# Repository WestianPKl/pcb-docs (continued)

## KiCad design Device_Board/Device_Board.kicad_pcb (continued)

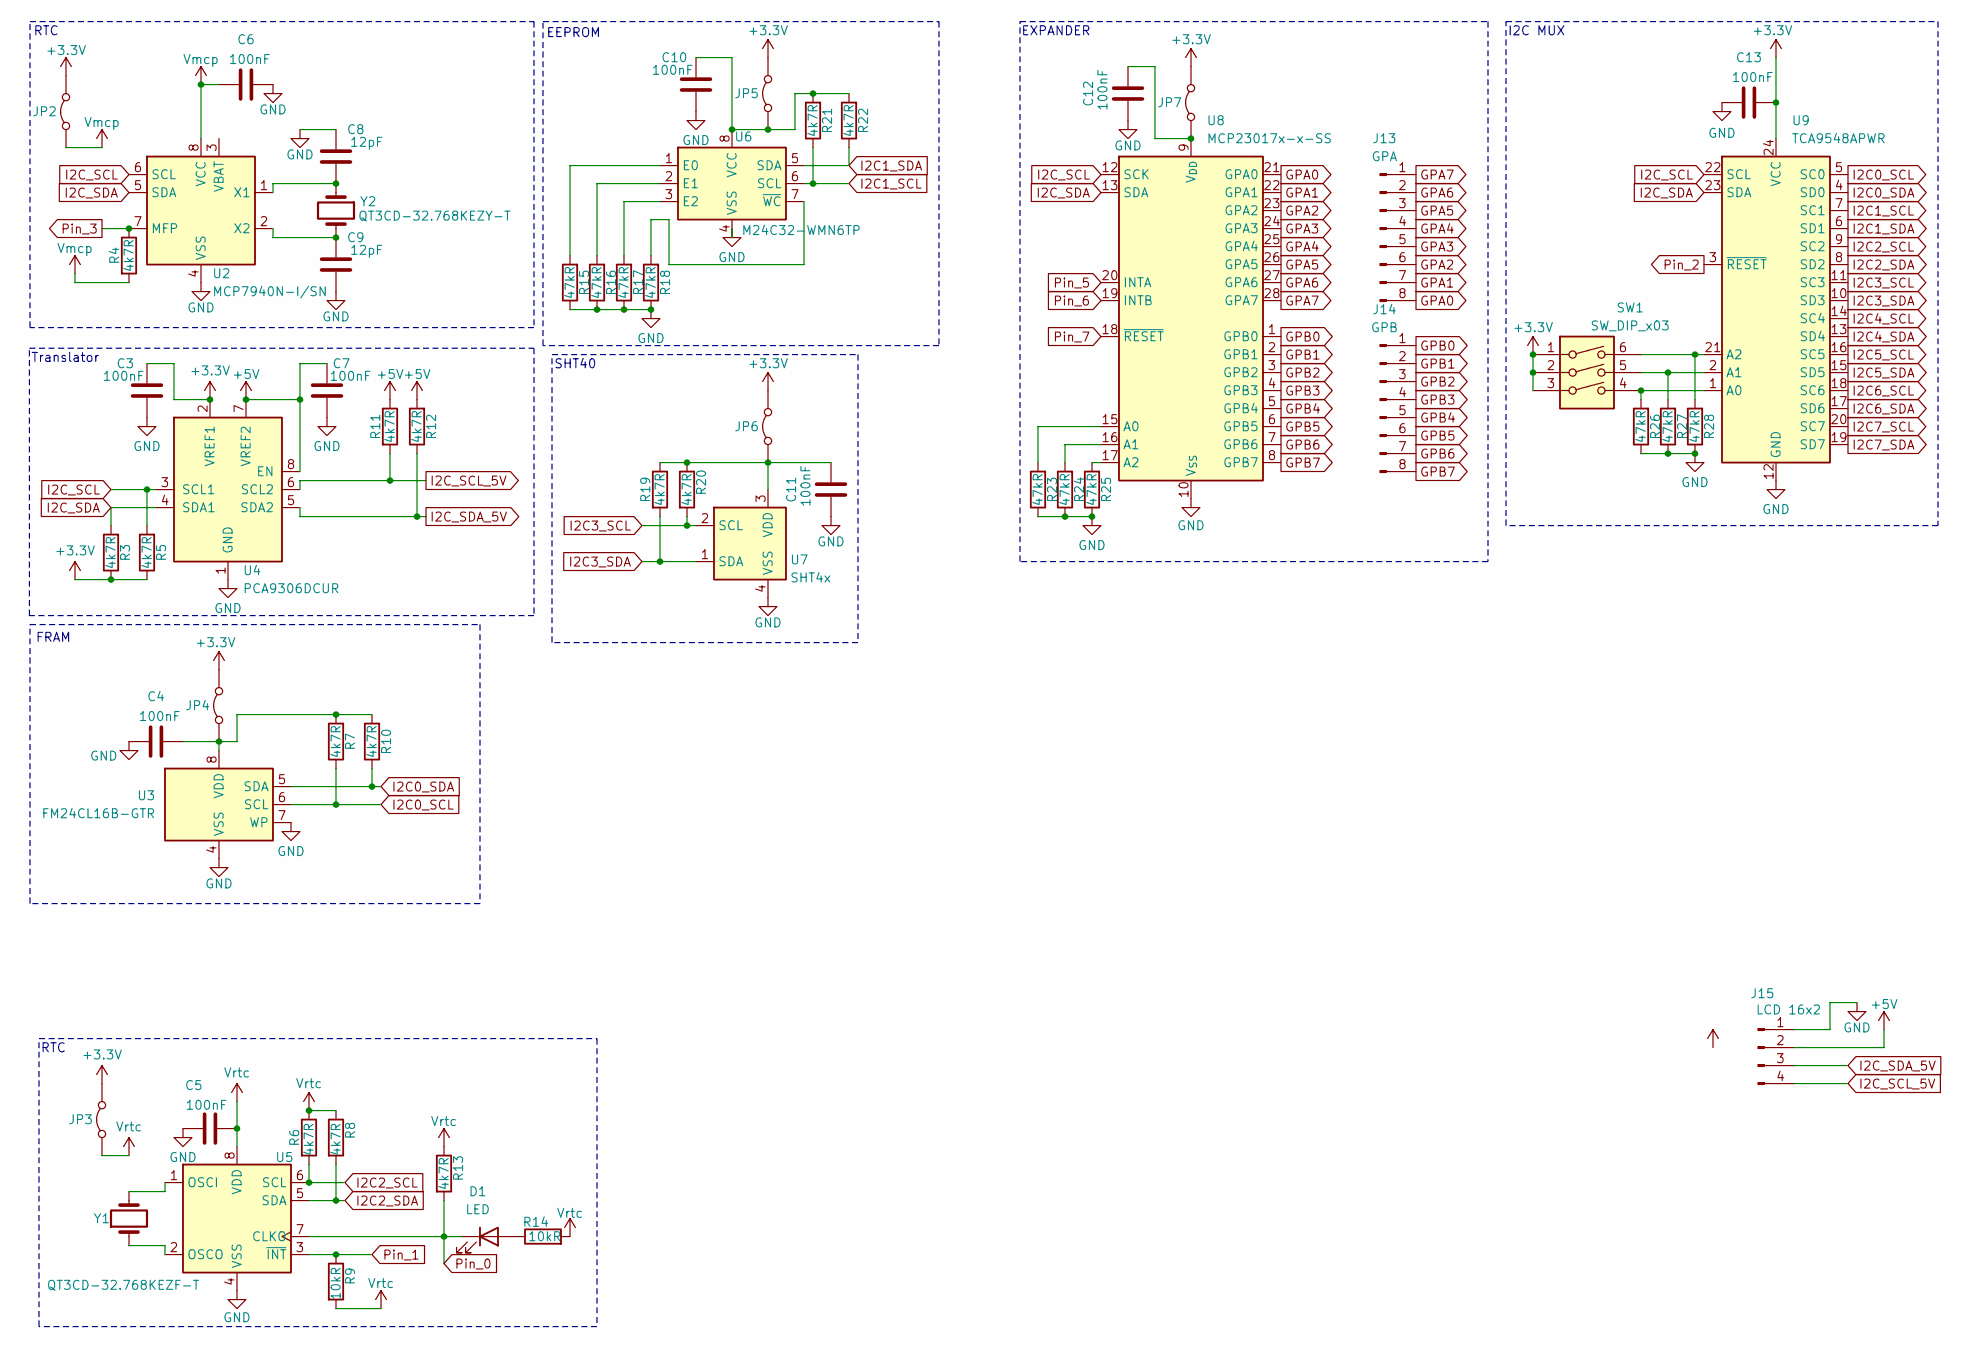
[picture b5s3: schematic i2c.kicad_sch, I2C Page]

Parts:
C3, C4, C5, C6, C7, C10, C11, C12, C13: 100nF; C_0603_1608Metric
C8, C9: 12pF; C_0603_1608Metric
D1: LED; LED_0603_1608Metric
J13: GPA; PinHeader_1x08_P2.54mm_Vertical
J14: GPB; PinHeader_1x08_P2.54mm_Vertical
J15: LCD 16x2; PinHeader_1x04_P2.54mm_Vertical
JP2, JP3, JP4, JP5, JP6, JP7: Jumper_2_Bridged; PinHeader_1x02_P2.54mm_Vertical
R3, R4, R5, R6, R7, R8, R10, R11, R12, R13, R19, R20, R21, R22: 4k7R; R_0603_1608Metric
R9, R14: 10kR; R_0603_1608Metric
R15, R16, R17, R18, R23, R24, R25, R26, R27, R28: 47kR; R_0603_1608Metric
SW1: SW_DIP_x03; SW_DIP_SPSTx03_Slide_9.78x9.8mm_W7.62mm_P2.54mm
U2: MCP7940N-I/SN; SOIC-8_3.9x4.9mm_P1.27mm
U3: FM24CL16B-GTR; SOIC-8_3.9x4.9mm_P1.27mm
U4: PCA9306DCUR; VSSOP-8_2.3x2mm_P0.5mm
U5: PCF8563T; SOIC-8_3.9x4.9mm_P1.27mm
U6: M24C32-WMN6TP; SOIC-8_3.9x4.9mm_P1.27mm
U7: SHT4x; Sensirion_DFN-4_1.5x1.5mm_P0.8mm_SHT4x_NoCentralPad
U8: MCP23017x-x-SS; SSOP-28_5.3x10.2mm_P0.65mm
U9: TCA9548APWR; TSSOP-24_4.4x7.8mm_P0.65mm
Y1: QT3CD-32.768KEZF-T; Crystal_SMD_3215-2Pin_3.2x1.5mm
Y2: QT3CD-32.768KEZY-T; Crystal_SMD_3215-2Pin_3.2x1.5mm

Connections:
+3.3V: C3.1, C13.1, JP2.2 (B), JP3.2 (B), JP4.2 (B), JP5.2 (B), JP6.2 (B), JP7.2 (B), R3.1, R5.1, SW1.1, SW1.2, SW1.3, U4.2 (VREF1), U9.24 (VCC); also elsewhere on the board
+5V: C7.1, J15.2, R11.1, R12.2, U4.7 (VREF2), U4.8 (EN); also elsewhere on the board
GND: C3.2, C4.2, C5.2, C6.1, C7.2, C8.2, C9.1, C10.2, C11.2, C12.2, C13.2, J15.1, R15.1, R16.1, R17.1, R18.1, R23.1, R24.1, R25.1, R26.1, R27.1, R28.1, U2.4 (VSS), U3.4 (VSS), U3.7 (WP), U4.1 (GND), U5.4 (VSS), U6.4 (VSS), U7.4 (VSS), U8.10 (V_{SS}), U9.12 (GND); also elsewhere on the board
GPA0: J13.8, U8.21 (GPA0)
GPA1: J13.7, U8.22 (GPA1)
GPA2: J13.6, U8.23 (GPA2)
GPA3: J13.5, U8.24 (GPA3)
GPA4: J13.4, U8.25 (GPA4)
GPA5: J13.3, U8.26 (GPA5)
GPA6: J13.2, U8.27 (GPA6)
GPA7: J13.1, U8.28 (GPA7)
GPB0: J14.1, U8.1 (GPB0)
GPB1: J14.2, U8.2 (GPB1)
GPB2: J14.3, U8.3 (GPB2)
GPB3: J14.4, U8.4 (GPB3)
GPB4: J14.5, U8.5 (GPB4)
GPB5: J14.6, U8.6 (GPB5)
GPB6: J14.7, U8.7 (GPB6)
GPB7: J14.8, U8.8 (GPB7)
I2C0_SCL: R7.1, U3.6 (SCL), U9.5 (SC0)
I2C0_SDA: R10.1, U3.5 (SDA), U9.4 (SD0)
I2C1_SCL: R21.1, U6.6 (SCL), U9.7 (SC1)
I2C1_SDA: R22.1, U6.5 (SDA), U9.6 (SD1)
I2C2_SCL: R6.2, U5.6 (SCL), U9.9 (SC2)
I2C2_SDA: R8.2, U5.5 (SDA), U9.8 (SD2)
I2C3_SCL: R20.2, U7.2 (SCL), U9.11 (SC3)
I2C3_SDA: R19.2, U7.1 (SDA), U9.10 (SD3)
I2C4_SCL: U9.14 (SC4)
I2C4_SDA: U9.13 (SD4)
I2C5_SCL: U9.16 (SC5)
I2C5_SDA: U9.15 (SD5)
I2C6_SCL: U9.18 (SC6)
I2C6_SDA: U9.17 (SD6)
I2C7_SCL: U9.20 (SC7)
I2C7_SDA: U9.19 (SD7)
I2C_SCL: R5.2, U2.6 (SCL), U4.3 (SCL1), U8.12 (SCK), U9.22 (SCL); also elsewhere on the board
I2C_SCL_5V: J15.4, R11.2, U4.6 (SCL2)
I2C_SDA: R3.2, U2.5 (SDA), U4.4 (SDA1), U8.13 (SDA), U9.23 (SDA); also elsewhere on the board
I2C_SDA_5V: J15.3, R12.1, U4.5 (SDA2)
unnamed: D1.2 (A), R14.1
unnamed: C4.1, JP4.1 (A), R7.2, R10.2, U3.8 (VDD)
unnamed: C10.1, JP5.1 (A), R21.2, R22.2, U6.8 (VCC)
unnamed: C11.1, JP6.1 (A), R19.1, R20.1, U7.3 (VDD)
unnamed: C12.1, JP7.1 (A), U8.9 (V_{DD})
unnamed: C8.1, U2.1 (X1), Y2.1
unnamed: C9.2, U2.2 (X2), Y2.2
unnamed: U5.1 (OSCI), Y1.2
unnamed: U5.2 (OSCO), Y1.1
unnamed: R15.2, U6.1 (E0)
unnamed: R16.2, U6.2 (E1)
unnamed: R17.2, U6.3 (E2)
unnamed: R18.2, U6.7 (~WC)
unnamed: R23.2, U8.15 (A0)
unnamed: R24.2, U8.16 (A1)
unnamed: R25.2, U8.17 (A2)
unnamed: R26.2, SW1.4, U9.1 (A0)
unnamed: R27.2, SW1.5, U9.2 (A1)
unnamed: R28.2, SW1.6, U9.21 (A2)
Pin_0: D1.1 (K), R13.2, U5.7 (CLKO); also elsewhere on the board
Pin_1: R9.1, U5.3 (~INT); also elsewhere on the board
Pin_2: U9.3 (~RESET); also elsewhere on the board
Pin_3: R4.1, U2.7 (MFP); also elsewhere on the board
Pin_5: U8.20 (INTA); also elsewhere on the board
Pin_6: U8.19 (INTB); also elsewhere on the board
Pin_7: U8.18 (~RESET); also elsewhere on the board
Vmcp: C6.2, JP2.1 (A), R4.2, U2.8 (VCC)
Vrtc: C5.1, JP3.1 (A), R6.1, R8.1, R9.2, R13.1, R14.2, U5.8 (VDD)

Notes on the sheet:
RTC
FRAM
EEPROM
I2C MUX
Translator
SHT40
EXPANDER

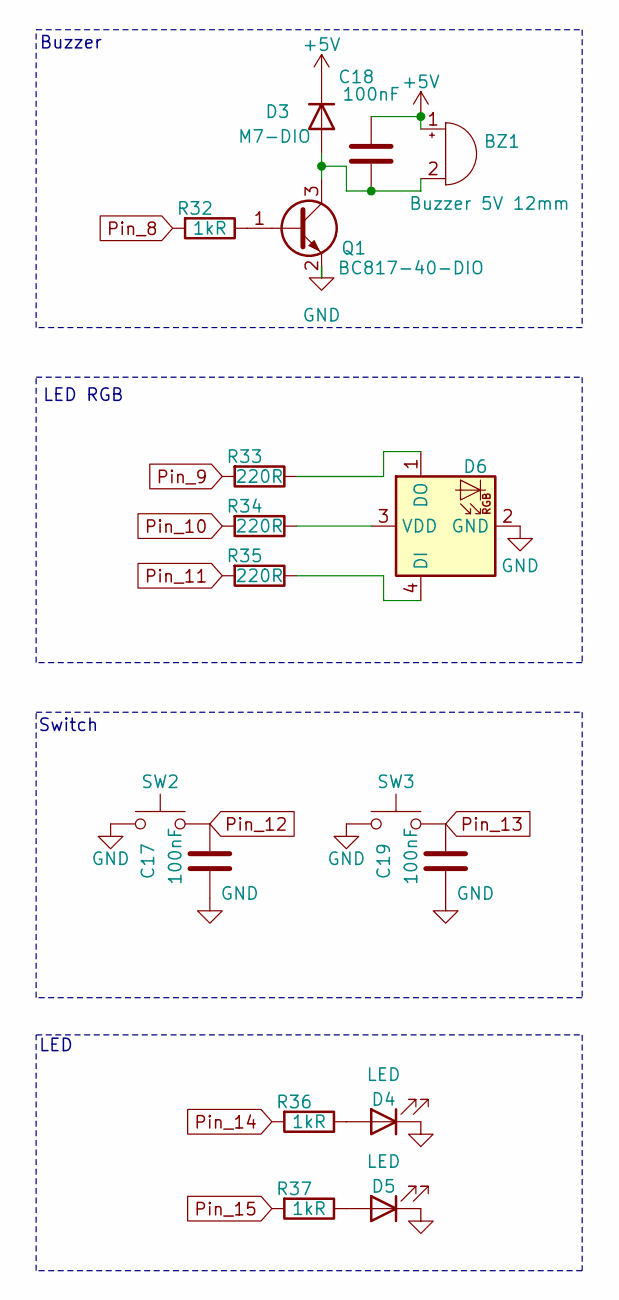
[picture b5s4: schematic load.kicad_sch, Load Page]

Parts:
BZ1: Buzzer 5V 12mm; Buzzer_12x9.5RM7.6
C17, C18, C19: 100nF; C_0603_1608Metric
D3: M7-DIO; D_SMA
D4, D5: LED; LED_0603_1608Metric
D6: OSTBPCS2C2B; LED_Avago_PLCC4_3.2x2.8mm_CW
Q1: BC817-40-DIO; SOT-23
R32, R36, R37: 1kR; R_0603_1608Metric
R33, R34, R35: 220R; R_0603_1608Metric
SW2, SW3: Tact Switch 6x6mm / 13mm; SW_PUSH_6mm

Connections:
+5V: BZ1.1 (+), C18.2, D3.1 (K); also elsewhere on the board
GND: C17.2, C19.2, D4.1 (K), D5.1 (K), D6.2 (GND), Q1.2 (E), SW2.1, SW3.1; also elsewhere on the board
unnamed: BZ1.2 (-), C18.1, D3.2 (A), Q1.3 (C)
unnamed: D4.2 (A), R36.1
unnamed: D5.2 (A), R37.1
unnamed: D6.4 (DI), R35.1
unnamed: D6.1 (DO), R33.1
unnamed: D6.3 (VDD), R34.1
unnamed: Q1.1 (B), R32.1
Pin_8: R32.2; also elsewhere on the board
Pin_9: R33.2; also elsewhere on the board
Pin_10: R34.2; also elsewhere on the board
Pin_11: R35.2; also elsewhere on the board
Pin_12: C17.1, SW2.2; also elsewhere on the board
Pin_13: C19.1, SW3.2; also elsewhere on the board
Pin_14: R36.2; also elsewhere on the board
Pin_15: R37.2; also elsewhere on the board

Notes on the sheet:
LED RGB
LED
Buzzer
Switch

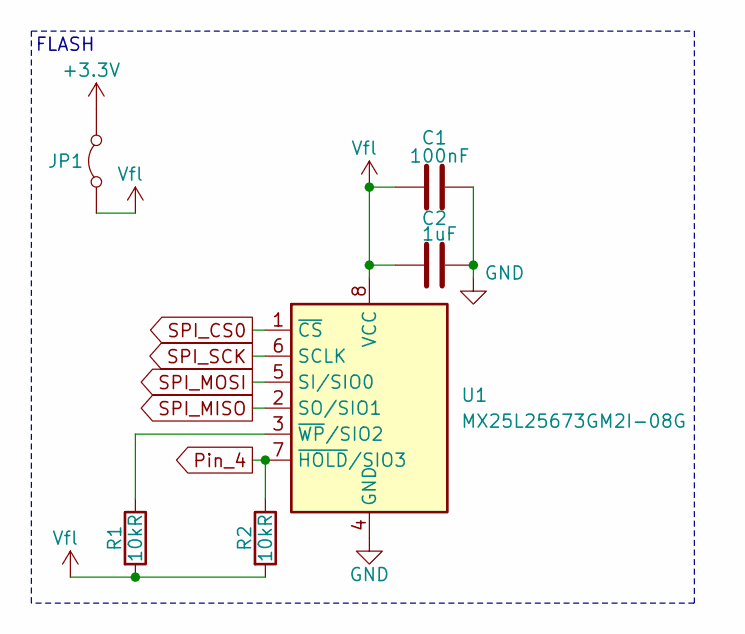
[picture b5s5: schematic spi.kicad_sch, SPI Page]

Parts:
C1: 100nF; C_0603_1608Metric
C2: 1uF; C_0603_1608Metric
JP1: Jumper_2_Bridged; PinHeader_1x02_P2.54mm_Vertical
R1, R2: 10kR; R_0603_1608Metric
U1: MX25L25673GM2I-08G; SOIC-8_5.3x5.3mm_P1.27mm

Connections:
+3.3V: JP1.2 (B); also elsewhere on the board
GND: C1.1, C2.1, U1.4 (GND); also elsewhere on the board
unnamed: R1.1, U1.3 (~WP/SIO2)
Pin_4: R2.1, U1.7 (~HOLD/SIO3); also elsewhere on the board
SPI_CS0: U1.1 (~CS)
SPI_MISO: U1.2 (SO/SIO1); also elsewhere on the board
SPI_MOSI: U1.5 (SI/SIO0); also elsewhere on the board
SPI_SCK: U1.6 (SCLK); also elsewhere on the board
Vfl: C1.2, C2.2, JP1.1 (A), R1.2, R2.2, U1.8 (VCC)

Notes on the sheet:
FLASH

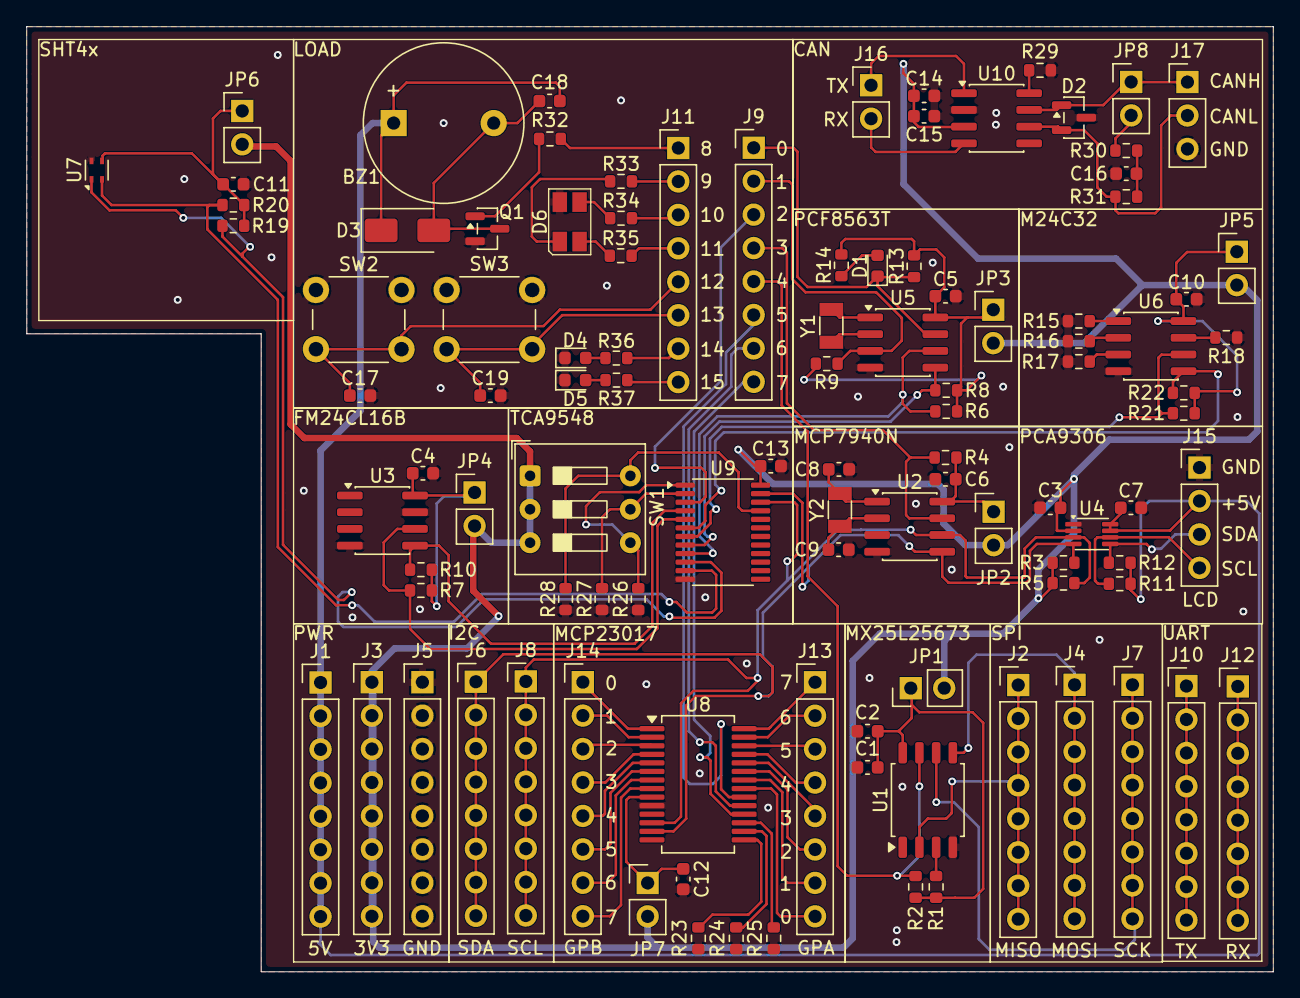
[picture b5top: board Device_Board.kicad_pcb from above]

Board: 2 copper layers, 94.7 x 71.8 mm, 104 parts (0 on the bottom side), 89 nets.
